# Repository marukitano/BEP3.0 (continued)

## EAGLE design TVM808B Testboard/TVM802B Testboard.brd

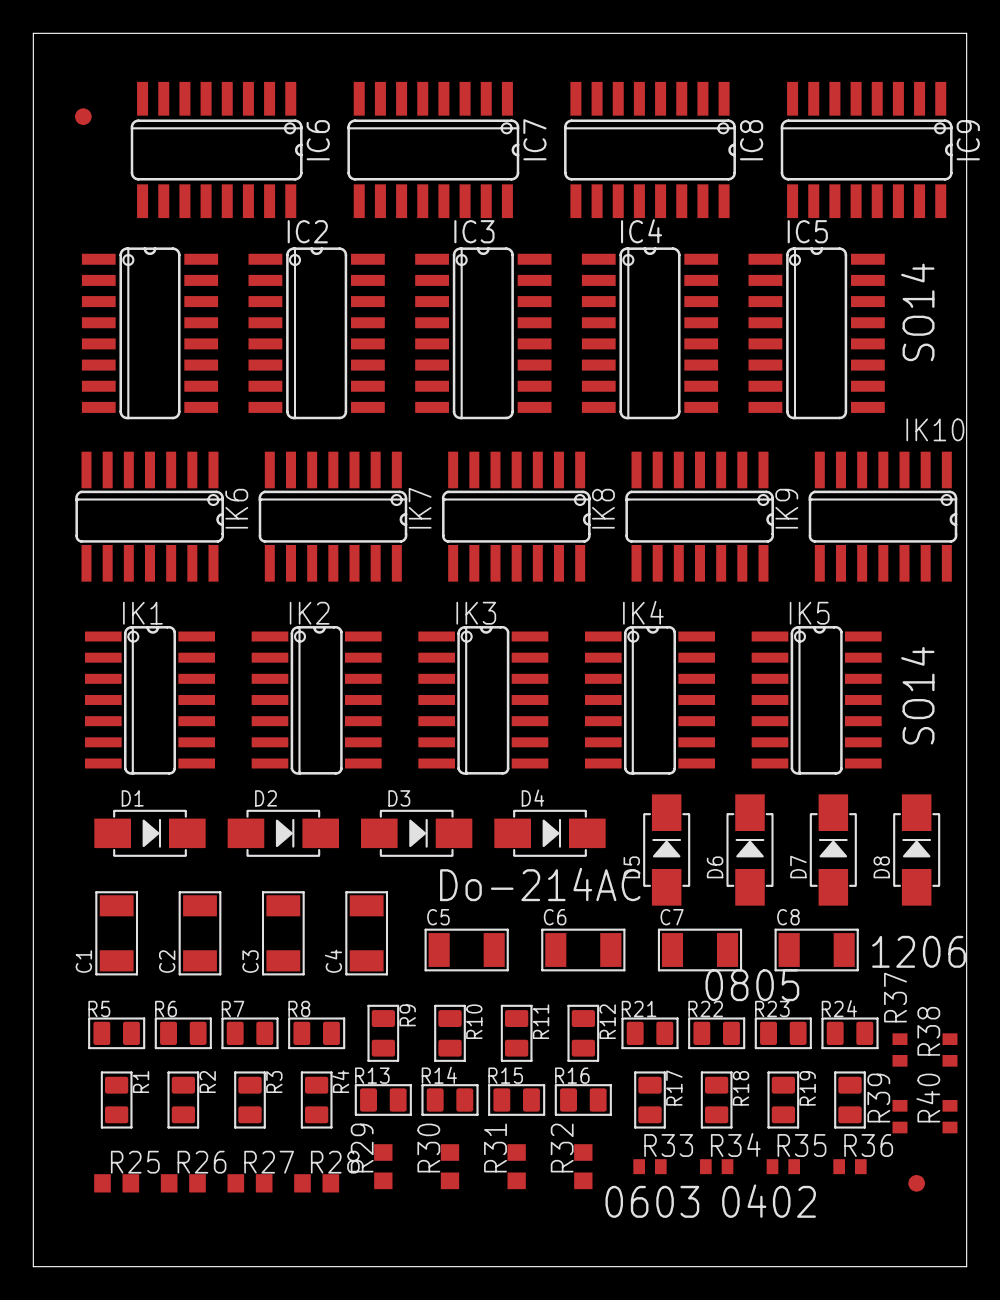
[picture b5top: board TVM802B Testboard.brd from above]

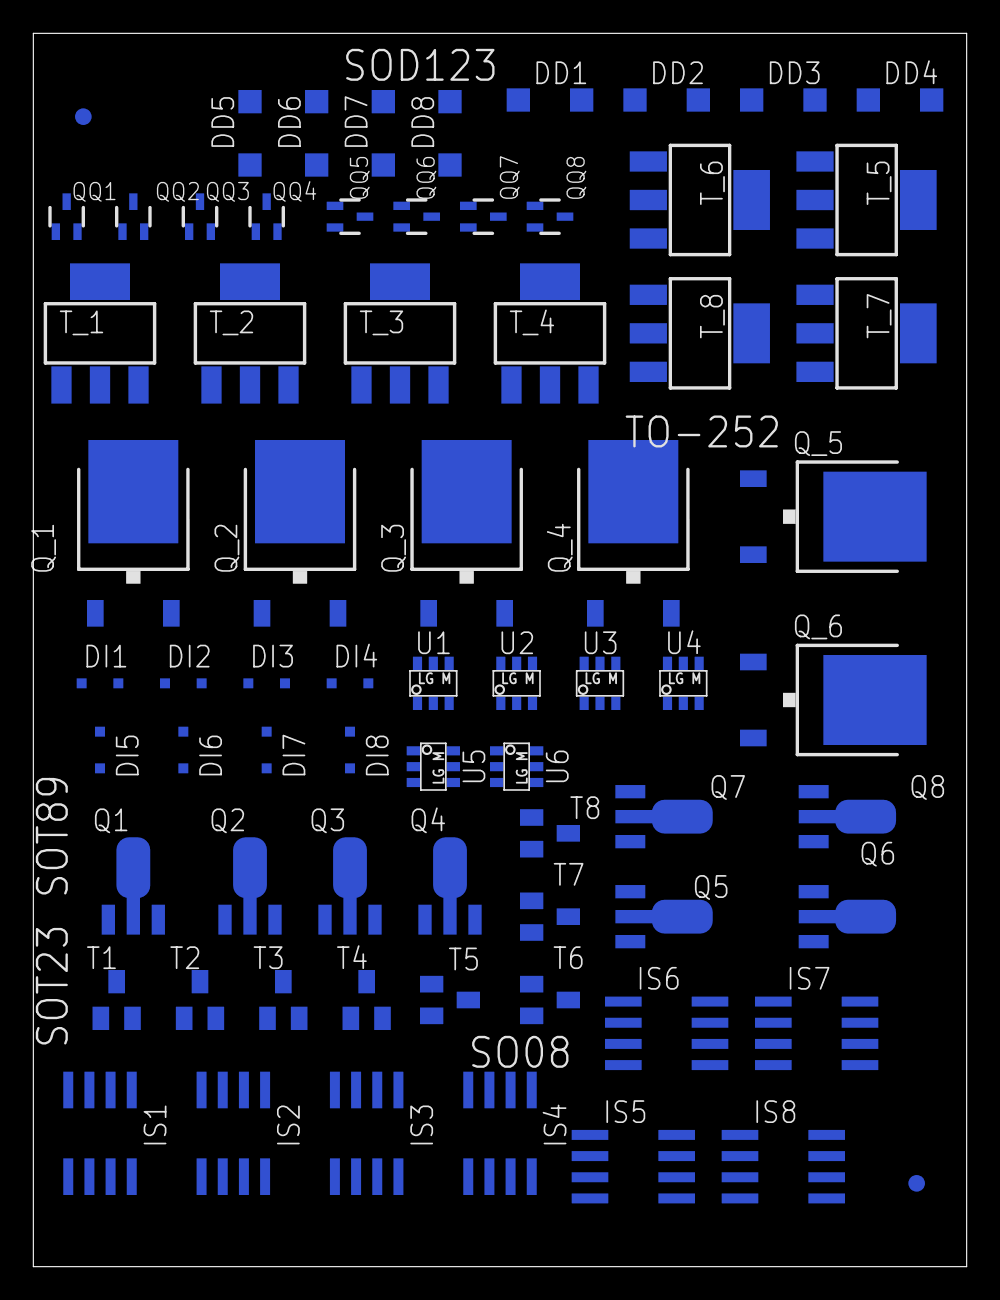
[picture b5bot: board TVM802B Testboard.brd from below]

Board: 2 copper layers, 56.0 x 74.0 mm, 147 parts (70 on the bottom side), 4 nets, no tracks yet.

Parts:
C1, C2, C3, C4, C5, C6, C7, C8: 100u; C1206
D1, D2, D3, D4, D5, D6, D7, D8: 1N4007; DO-214AC
DD1, DD2, DD3, DD4, DD5, DD6, DD7, DD8: SOD123
DI1, DI2, DI3, DI4, DI5, DI6, DI7, DI8: SOD323-R
FID1_: FID2; FIDUCIAL_1MM
FID2: FID1; FIDUCIAL_1MM
FID3_, FID4: FIDUCIAL; FIDUCIAL_1MM
IC1, IC2, IC3, IC4, IC5, IC6, IC7, IC8, IC9: 4028; SO16
IK1, IK2, IK3, IK4, IK5, IK6, IK7, IK8, IK9, IK10: LM339; SO14
IS1, IS2, IS3, IS4, IS5, IS6, IS7, IS8: 555; SO08
Q1, Q2, Q3, Q4, Q5, Q6, Q7, Q8: MY; SOT89
QQ1, QQ2, QQ3, QQ4, QQ5, QQ6, QQ7, QQ8: SOT323
Q_1, Q_2, Q_3, Q_4, Q_5, Q_6: SPD30P06PTO252; TO252
R1, R2, R3, R4, R5, R6, R7, R8, R9, R10, R11, R12, R13, R14, R15, R16, R17, R18, R19, R20, R21, R22, R23, R24: 4701; R0805
R25, R26, R27, R28, R29, R30, R31, R32: R0603
R33, R34, R35, R36, R37, R38, R39, R40: R0402
T1, T2, T3, T4, T5, T6, T7, T8: J1; SOT23-BEC
T_1, T_2, T_3, T_4, T_5, T_6, T_7, T_8: SOT223
U1, U2, U3, U4, U5, U6: NUP4304SOT457_R; SOT457R_PHILIPS

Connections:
GND: IK1.12, IK2.12, IK3.12, IK4.12, IK5.12, IK6.12, IK7.12, IK8.12, IK9.12, IK10.12, IS1.1, IS2.1, IS3.1, IS4.1, IS5.1, IS6.1, IS7.1, IS8.1
V+: IK1.3, IK2.3, IK3.3, IK4.3, IK5.3, IK6.3, IK7.3, IK8.3, IK9.3, IK10.3, IS1.8, IS2.8, IS3.8, IS4.8, IS5.8, IS6.8, IS7.8, IS8.8
VDD: IC1.16, IC2.16, IC3.16, IC4.16, IC5.16, IC6.16, IC7.16, IC8.16, IC9.16
VSS: IC1.8, IC2.8, IC3.8, IC4.8, IC5.8, IC6.8, IC7.8, IC8.8, IC9.8

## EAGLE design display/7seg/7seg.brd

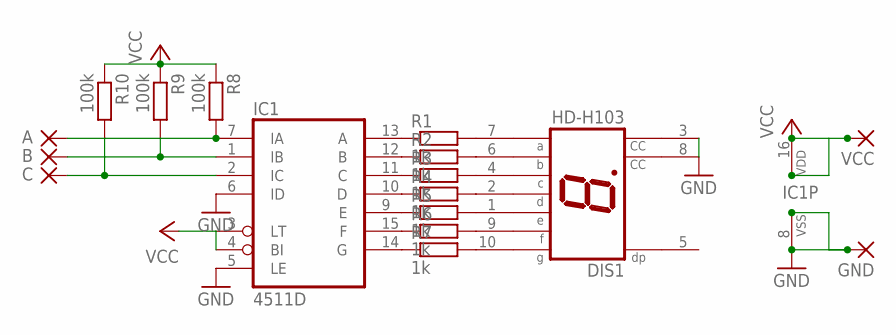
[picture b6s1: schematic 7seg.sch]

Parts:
A: 1,6/0,9
B: 1,6/0,9
C: 1,6/0,9
DIS1: HD-H103; HDSP-M
GND: 1,6/0,9
IC1: 4511D; SO16
R1, R2, R3, R4, R5, R6, R7: 1k; R0805
R8, R9, R10: 100k; R0805
VCC: 1,6/0,9

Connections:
GND: DIS1.3 (CC), DIS1.8 (CC), IC1.5 (LE), IC1.6 (ID), IC1.8 (VSS)
unnamed: IC1.13 (A), R1.1
unnamed: DIS1.7 (A), R1.2
unnamed: IC1.12 (B), R2.1
unnamed: DIS1.6 (B), R2.2
unnamed: IC1.11 (C), R3.1
unnamed: DIS1.4 (C), R3.2
unnamed: IC1.10 (D), R4.1
unnamed: DIS1.2 (D), R4.2
unnamed: IC1.9 (E), R5.1
unnamed: DIS1.1 (E), R5.2
unnamed: IC1.15 (F), R6.1
unnamed: DIS1.9 (F), R6.2
unnamed: IC1.14 (G), R7.1
unnamed: DIS1.10 (G), R7.2
unnamed: A.1, IC1.7 (IA), R8.2
unnamed: B.1, IC1.1 (IB), R9.2
unnamed: C.1, IC1.2 (IC), R10.2
VCC: IC1.3 (LT), IC1.4 (BI), IC1.16 (VDD), R8.1, R9.1, R10.1

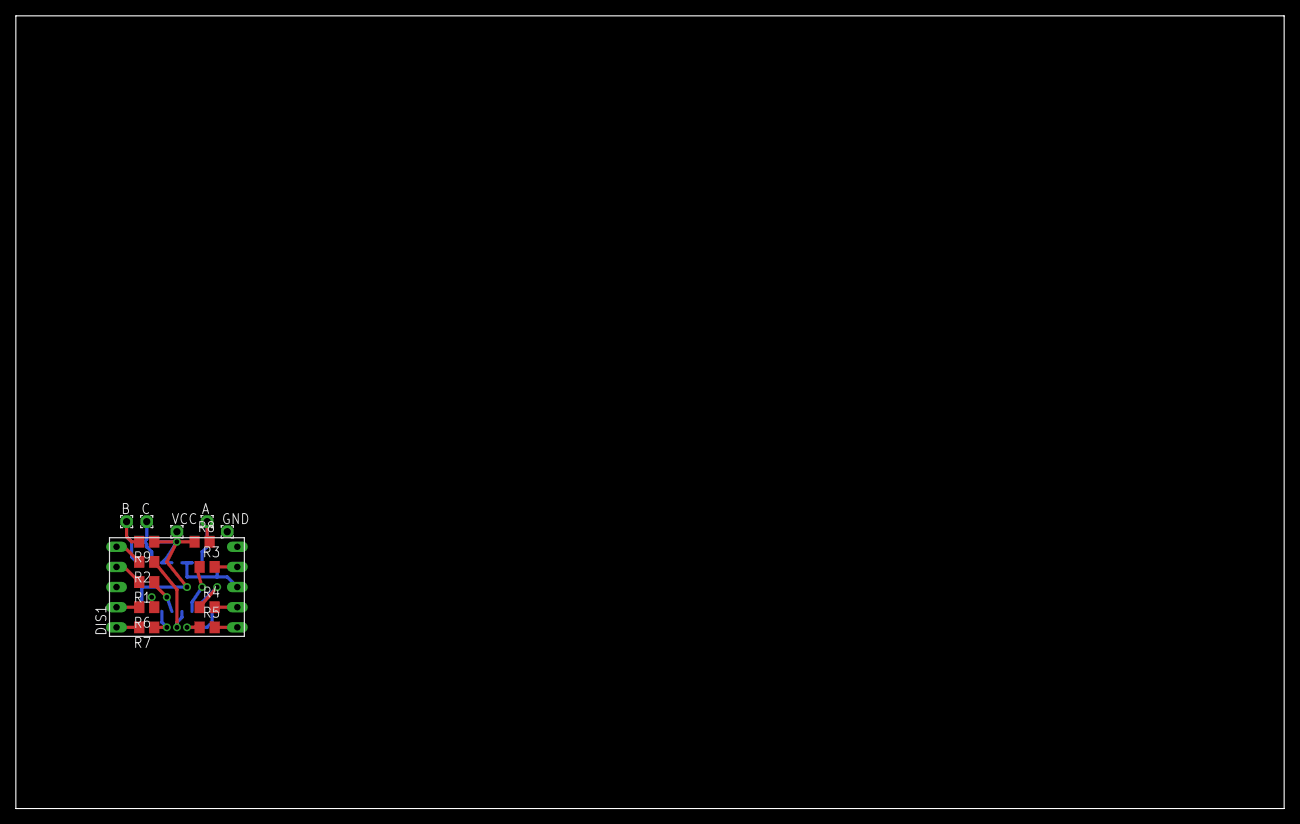
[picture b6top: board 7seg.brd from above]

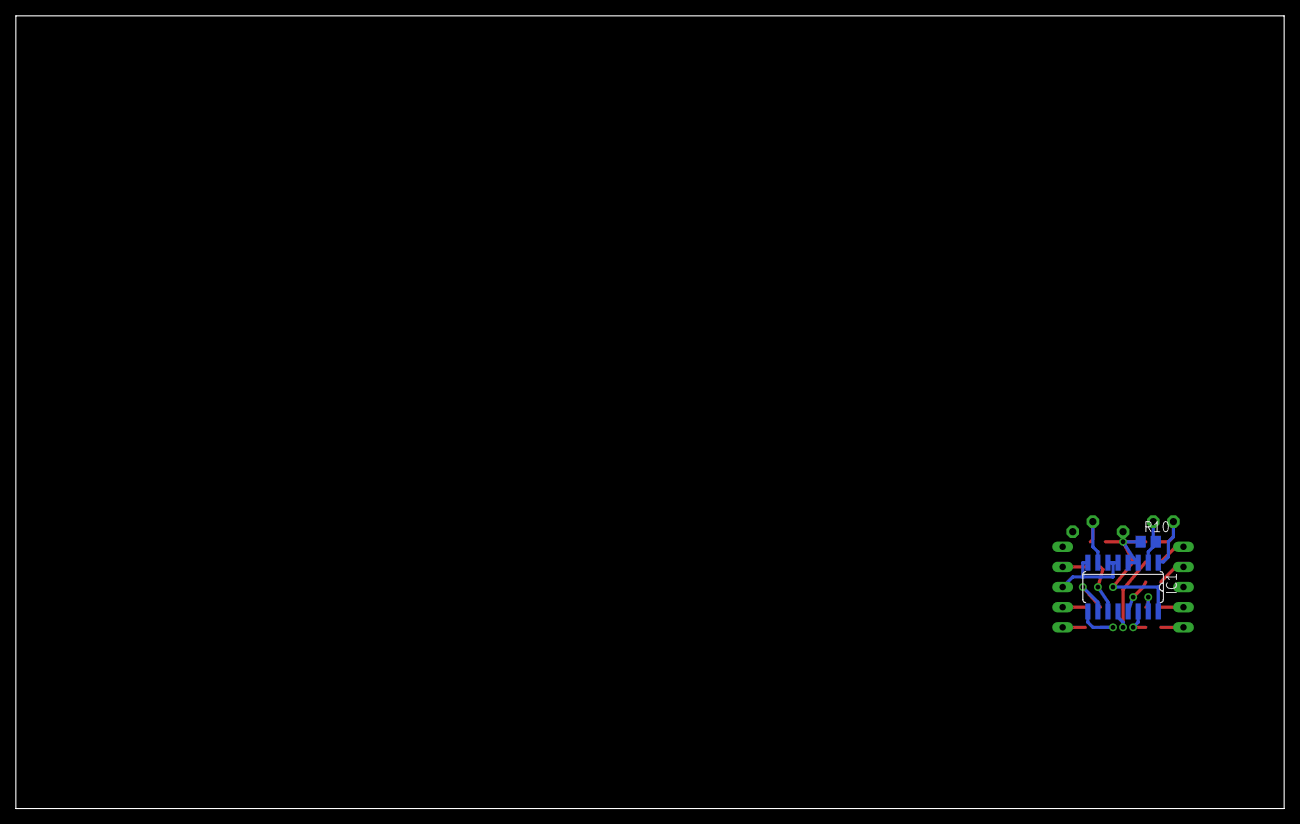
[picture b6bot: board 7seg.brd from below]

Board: 2 copper layers, 160.0 x 100.0 mm, 17 parts (2 on the bottom side), 19 nets.

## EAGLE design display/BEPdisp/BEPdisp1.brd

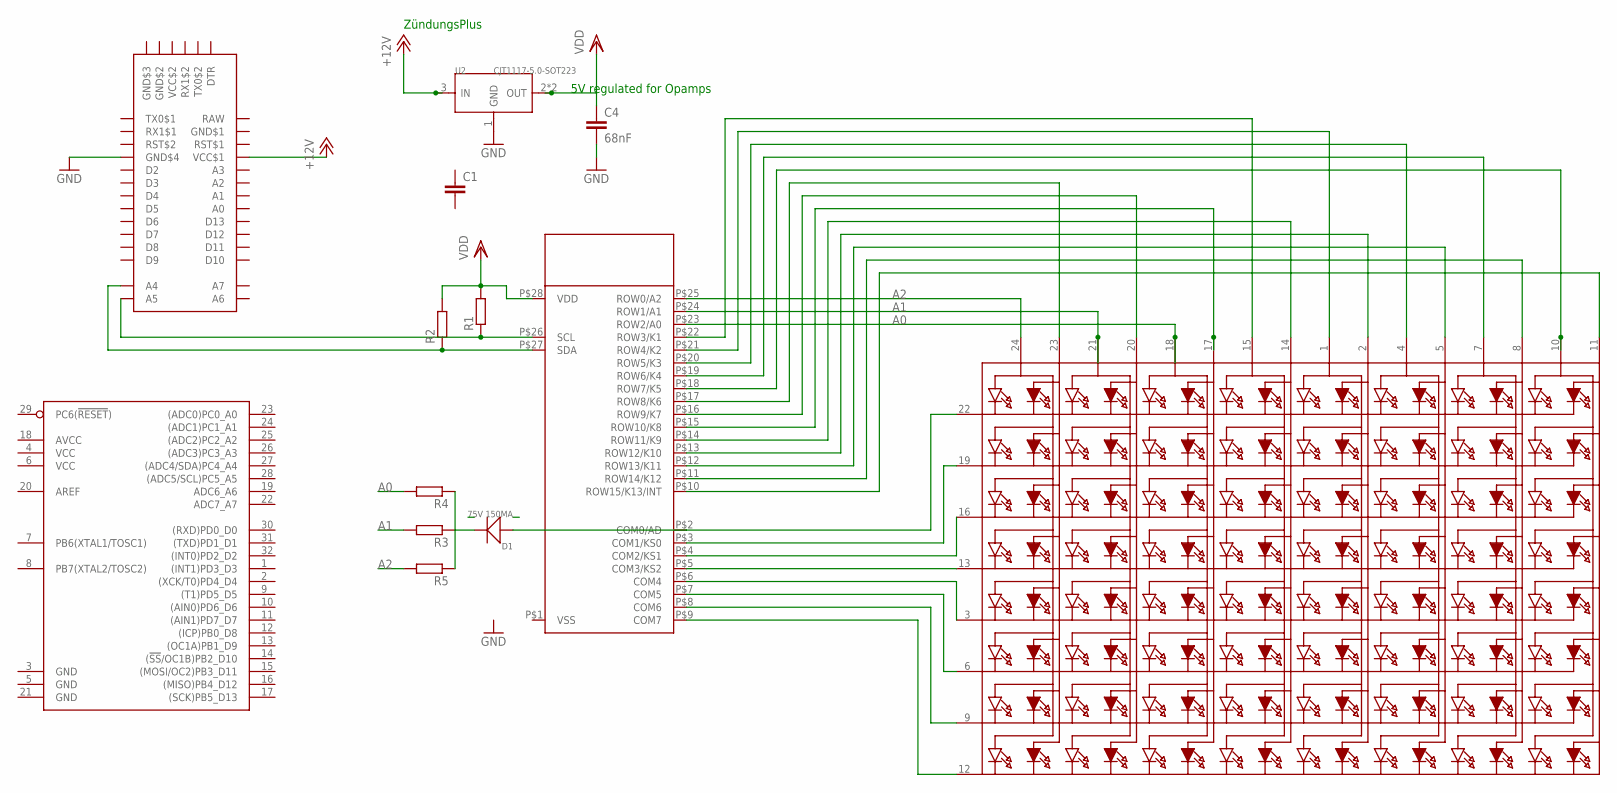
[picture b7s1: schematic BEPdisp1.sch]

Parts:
C1: C-EUC0805; C0805
C4: 68nF; C1206K
D1: 75V 150MA; LED-1206
IC1: ATMEGA48A-ARDUINO-TQFP; TQFP32-08
LED1: SEGMENT_8X8_BICOLOR_ROWCATHODEMI2A883XX; SEGMENT_BICOL_BL-M12A883XX
R1, R2, R3, R4, R5: R-EU_R0805; R0805
U1: HT16K33-SOP28; SOP-28
U2: CJT1117-5.0-SOT223; SOT-223
U$1: ARDUINO_PRO_MINI

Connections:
+12V: U2.3 (IN), U$1.VCC$1
A0: LED1.18 (A5), R4.2, U1.P$23 (ROW2/A0)
A1: LED1.21 (A3), R3.2, U1.P$24 (ROW1/A1)
A2: LED1.24 (A1), R5.2, U1.P$25 (ROW0/A2)
AVCC: IC1.18 (AVCC)
GND: C4.2, IC1.3 (GND), IC1.5 (GND), IC1.21 (GND), U2.1 (GND), U$1.GND$4
GND$1: U$1.GDN$1 (GND$1)
GND$2: U$1.GND$2
GND$3: U$1.GND$3
unnamed: R1.1, U1.P$26 (SCL), U$1.A5
unnamed: R2.1, U1.P$27 (SDA), U$1.A4
unnamed: LED1.16 (K3), U1.P$4 (COM2/KS1)
unnamed: LED1.13 (K4), U1.P$5 (COM3/KS2)
unnamed: LED1.3 (K5), U1.P$6 (COM4)
unnamed: LED1.6 (K6), U1.P$7 (COM5)
unnamed: LED1.9 (K7), U1.P$8 (COM6)
unnamed: LED1.12 (K8), U1.P$9 (COM7)
unnamed: LED1.19 (K2), U1.P$3 (COM1/KS0)
unnamed: LED1.22 (K1), U1.P$2 (COM0/AD)
unnamed: LED1.15 (A7), U1.P$22 (ROW3/K1)
unnamed: LED1.1 (A9), U1.P$21 (ROW4/K2)
unnamed: LED1.4 (A11), U1.P$20 (ROW5/K3)
unnamed: LED1.7 (A13), U1.P$19 (ROW6/K4)
unnamed: LED1.10 (A15), U1.P$18 (ROW7/K5)
unnamed: LED1.23 (A2), U1.P$17 (ROW8/K6)
unnamed: LED1.20 (A4), U1.P$16 (ROW9/K7)
unnamed: LED1.17 (A6), U1.P$15 (ROW10/K8)
unnamed: LED1.14 (A8), U1.P$14 (ROW11/K9)
unnamed: LED1.2 (A10), U1.P$13 (ROW12/K10)
unnamed: LED1.5 (A12), U1.P$12 (ROW13/K11)
unnamed: LED1.8 (A14), U1.P$11 (ROW14/K12)
unnamed: LED1.11 (A16), U1.P$10 (ROW15/K13/INT)
unnamed: R4.1, R5.1
RAW: U$1.RAW
VCC: IC1.4 (VCC), IC1.6 (VCC)
VCC$2: U$1.VCC$2
VDD: C4.1, R1.2, R2.2, U1.P$28 (VDD), U2.2 (OUT), U2.TER (OUT)

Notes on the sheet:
5V regulated for Opamps
ZündungsPlus

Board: 2 copper layers, 13 parts (2 on the bottom side), 31 nets, no tracks yet.
